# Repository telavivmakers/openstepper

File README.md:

a method and appartues to control a servo motor in an affrodable manner. using an I2C protocl integarted on our current stepper driver IC, the PCA9629A  

PCA9629A 
** [datasheet](http://www.nxp.com/documents/application_note/AN11483.pdf) 
** [white paper] (http://www.nxp.com/documents/application_note/AN11483.pdf)
** [picture via whitepaper](http://i.imgur.com/x2pDNIk.jpg)
** [picture via datasheet](http://i.imgur.com/beChXN7.jpg)
** [mouser TSSOP-16	package](http://il.mouser.com/ProductDetail/NXP/PCA9629APWJ/?qs=%2fha2pyFaduirHsohZDD79V6Vp0RsOd1mHZBi0eZIx6U%3d)

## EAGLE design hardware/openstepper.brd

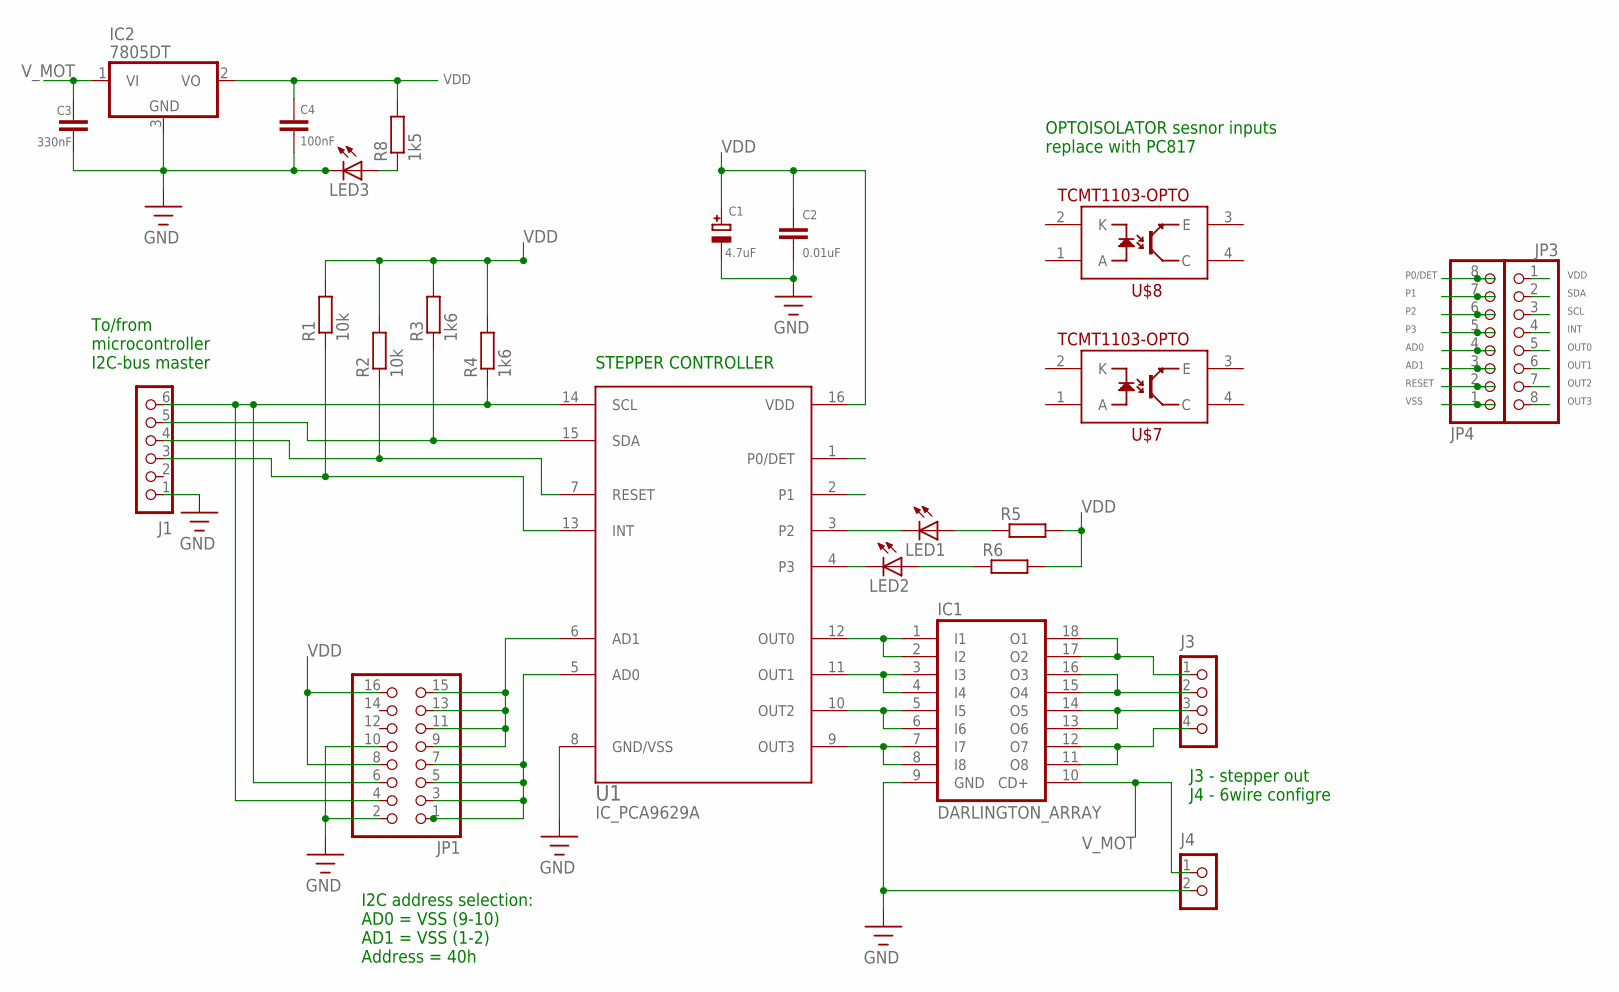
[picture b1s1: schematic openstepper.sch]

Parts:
C1: 4.7uF; PANASONIC_C
C2: 0.01uF; C805
C3: 330nF; C025-024X044
C4: 100nF; C025-024X044
IC1: DARLINGTON_ARRAY; SO-18
IC2: 7805DT; TO252
J1: CON_HEADER_1X06-PTH; M1X6
J3: CON_HEADER_1X04; M1X4
J4: CON_HEADER_1X02-PTH; M1X2
JP1: HEADER-2X8; 2X08
JP3, JP4: PINHD-1X8BIG; 1X08-BIG
LED1, LED2, LED3: LED-0805; LED-805
R1, R2: 10k; R1206
R3, R4: 1k6; R1206
R5, R6: RESISTORR805-0805; R805
R8: 1k5; R1206
U1: IC_PCA9629A; TSSOP-16
U$7, U$8: TCMT1103-OPTO; SSOP-4

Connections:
AD0: JP1.1, JP1.3, JP1.5, JP1.7, JP4.4, U1.5 (AD0)
AD1: JP1.9, JP1.11, JP1.13, JP1.15, JP4.3, U1.6 (AD1)
GND: C1.-, C2.2, C3.1, C4.1, IC1.9 (GND), IC2.3 (GND), J1.1, J4.2, JP1.2, JP1.10, LED3.C, U1.8 (GND/VSS)
INT: J1.3, JP3.4, R1.1, U1.13 (INT)
unnamed: LED3.A, R8.1
unnamed: IC1.17 (O2), IC1.18 (O1), J3.1
unnamed: IC1.15 (O4), IC1.16 (O3), J3.2
unnamed: IC1.13 (O6), IC1.14 (O5), J3.3
unnamed: IC1.11 (O8), IC1.12 (O7), J3.4
unnamed: LED1.A, R5.1
unnamed: LED2.A, R6.1
OUT0: IC1.1 (I1), IC1.2 (I2), JP3.5, U1.12 (OUT0)
OUT1: IC1.3 (I3), IC1.4 (I4), JP3.6, U1.11 (OUT1)
OUT2: IC1.5 (I5), IC1.6 (I6), JP3.7, U1.10 (OUT2)
OUT3: IC1.7 (I7), IC1.8 (I8), JP3.8, U1.9 (OUT3)
P0/DET: JP4.8, U1.1 (P0/DET)
P1: JP4.7, U1.2 (P1)
P2: JP4.6, LED1.C, U1.3 (P2)
P3: JP4.5, LED2.C, U1.4 (P3)
RESET: J1.4, JP4.2, R2.1, U1.7 (RESET)
SCL: J1.6, JP1.4, JP1.6, JP3.3, R4.1, U1.14 (SCL)
SDA: J1.5, JP3.2, R3.1, U1.15 (SDA)
VDD: C1.+, C2.1, C4.2, IC2.2 (VO), JP1.8, JP1.16, JP3.1, R1.2, R2.2, R3.2, R4.2, R5.2, R6.2, R8.2, U1.16 (VDD)
VSS: JP4.1

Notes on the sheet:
To/from microcontroller I2C-bus master
J3 - stepper out J4 - 6wire configre
STEPPER CONTROLLER
I2C address selection: AD0 = VSS (9-10) AD1 = VSS (1-2) Address = 40h
OPTOISOLATOR sesnor inputs replace with PC817

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
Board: 2 copper layers, 25 parts (0 on the bottom side), 25 nets, no tracks yet.

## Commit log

2014-12-10 Update README.md
    add a block diagram picture
2014-12-10 create library part for eagle
2014-12-10 schema with darlington array and controller
2014-12-10 change symbol in lib, schema updated
2014-12-10 schema update + datasheets
    missing power regulator and optocopler setup (change to PC817)
2014-12-10 added schema pdf
2014-12-10 rough board layout
    and split breakout into two parts, also fixed names and labels on
    breakout
2014-12-11 added 5v regulator to schema

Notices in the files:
parts and their libraries:
microbuilder: This work is placed in the public domain, and may be freely used for commercial and non-commercial work with the following conditions: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
SparkFun-DiscreteSemi: Licensing: CC v3.0 Share-Alike You are welcome to use this library for commercial purposes.
